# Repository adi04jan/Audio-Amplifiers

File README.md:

# Audio-Amplifiers
Audio Amplifier for creating a bass through low pass filter effect.

**IDE Used** : : [Autodesk Eagle](https://www.autodesk.com/products/eagle/overview)

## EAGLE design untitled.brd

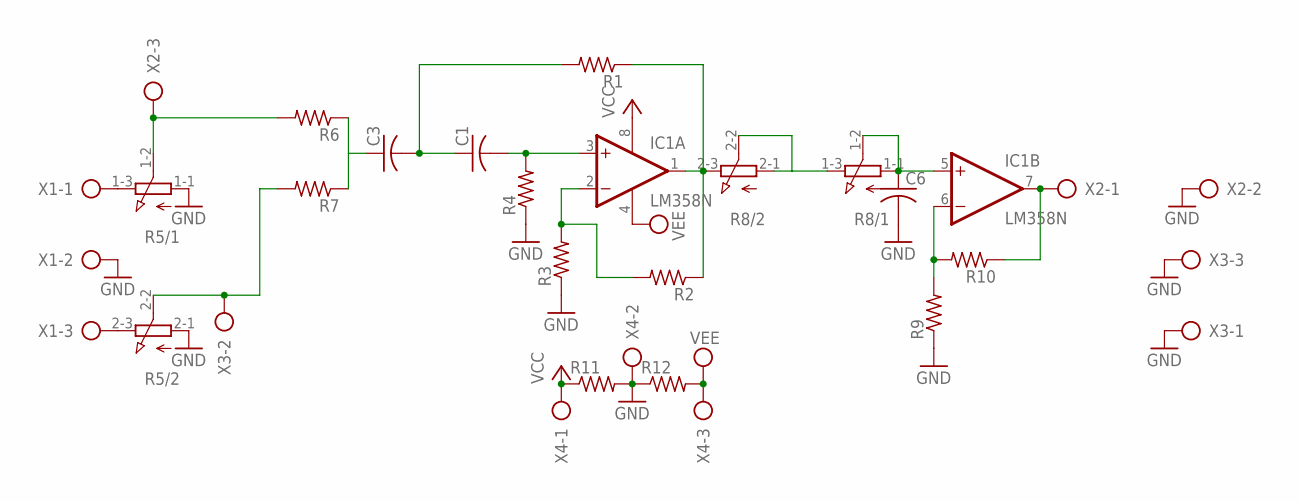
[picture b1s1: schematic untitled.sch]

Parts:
C1, C3, C6: C-US025-025X050; C025-025X050
IC1: LM358N; DIL08
R1, R2, R3, R4, R6, R7, R9, R10: FLIPFLOP-RES; 0805-THM
R5, R8: 3RP/1610G
R11, R12: R-US_0309/10; 0309/10
X1, X2, X3, X4: AK300/3

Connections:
GND: C6.2, R3.1, R4.1, R5.1-1 (A), R5.2-1 (A), R9.1, R11.2, R12.1, X1.2, X2.2, X3.1, X3.3, X4.2
unnamed: C1.2, IC1.3 (+IN), R4.2
unnamed: C1.1, C3.2, R1.2
unnamed: IC1.2 (-IN), R2.2, R3.2
unnamed: IC1.1 (OUT), R1.1, R2.1, R8.2-3 (E)
unnamed: R5.1-3 (E), X1.1
unnamed: R5.2-3 (E), X1.3
unnamed: C3.1, R6.1, R7.1
unnamed: R5.1-2 (S), R6.2, X2.3
unnamed: R5.2-2 (S), R7.2, X3.2
unnamed: C6.1, IC1.5 (+IN), R8.1-1 (A), R8.1-2 (S)
unnamed: R8.1-3 (E), R8.2-1 (A), R8.2-2 (S)
unnamed: IC1.6 (-IN), R9.2, R10.2
unnamed: IC1.7 (OUT), R10.1, X2.1
VCC: IC1.8 (V+), R11.1, X4.1
VEE: IC1.4 (V-), R12.2, X4.3

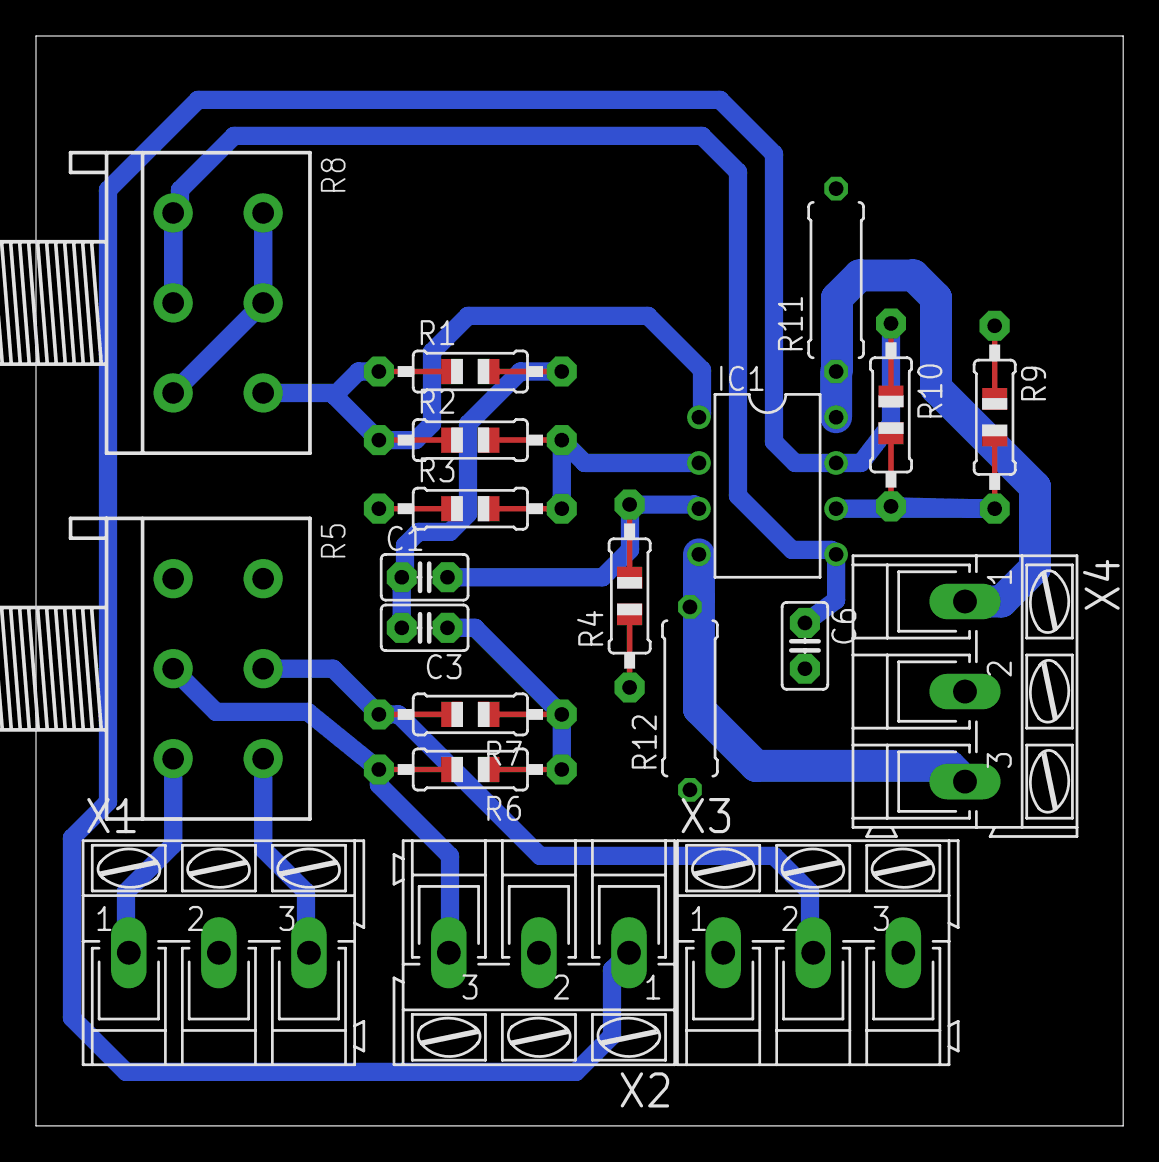
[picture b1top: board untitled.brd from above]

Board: 2 copper layers, 60.4 x 60.5 mm, 20 parts (0 on the bottom side), 16 nets.

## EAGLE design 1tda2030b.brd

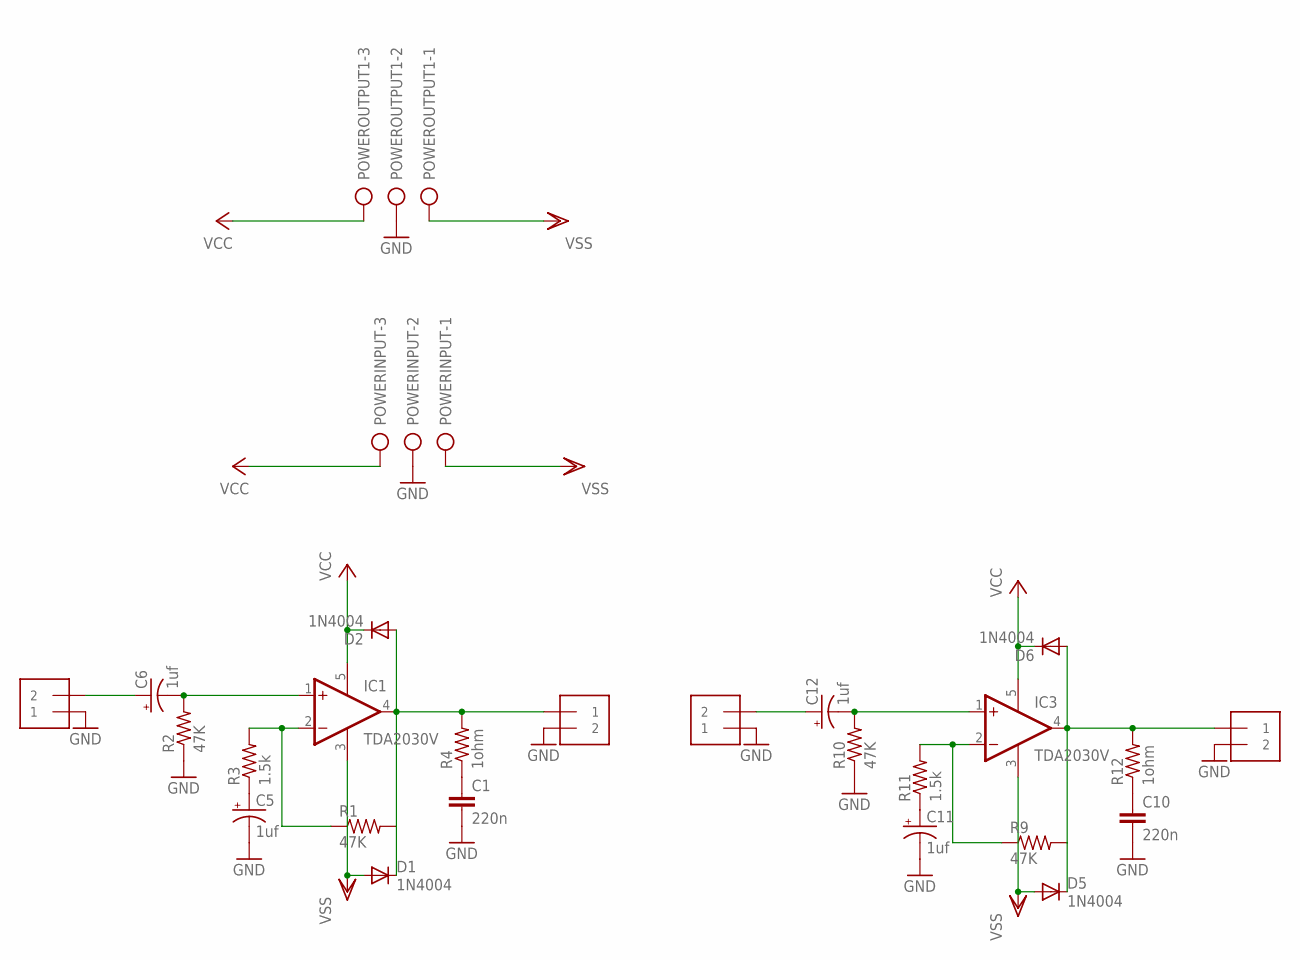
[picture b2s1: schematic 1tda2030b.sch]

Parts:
1STI/P, 1STO/P, 2NDI/P, 2NDO/P: 1X2-3.5MM
C1, C10: 220n; CAP-PTH-SMALL-KIT
C5, C6, C11, C12: 1uf; E5-8,5
D1, D2, D5, D6: 1N4004; DO41-10
IC1, IC3: TDA2030V; CB360
POWERINPUT: AK300/3
POWEROUTPUT1: AK300/3
R1, R2, R9, R10: 47K; 0805-THM
R3, R11: 1.5k; 0805-THM
R4, R12: 1ohm; 0805-THM

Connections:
GND: 1STI/P.1, 1STO/P.2, 2NDI/P.1, 2NDO/P.2, C1.2, C5.-, C10.2, C11.-, POWERINPUT.2, POWEROUTPUT1.2, R2.1, R10.1
unnamed: 1STO/P.1, D1.C, D2.A, IC1.4 (OUT), R1.2, R4.2
unnamed: C5.+, R3.1
unnamed: IC1.2 (-IN), R1.1, R3.2
unnamed: C1.1, R4.1
unnamed: 1STI/P.2, C6.+
unnamed: C6.-, IC1.1 (+IN), R2.2
unnamed: 2NDO/P.1, D5.C, D6.A, IC3.4 (OUT), R9.2, R12.2
unnamed: C11.+, R11.1
unnamed: IC3.2 (-IN), R9.1, R11.2
unnamed: C10.1, R12.1
unnamed: C12.-, IC3.1 (+IN), R10.2
unnamed: 2NDI/P.2, C12.+
VCC: D2.C, D6.C, IC1.5 (V+), IC3.5 (V+), POWERINPUT.3, POWEROUTPUT1.3
VSS: D1.A, D5.A, IC1.3 (GND), IC3.3 (GND), POWERINPUT.1, POWEROUTPUT1.1

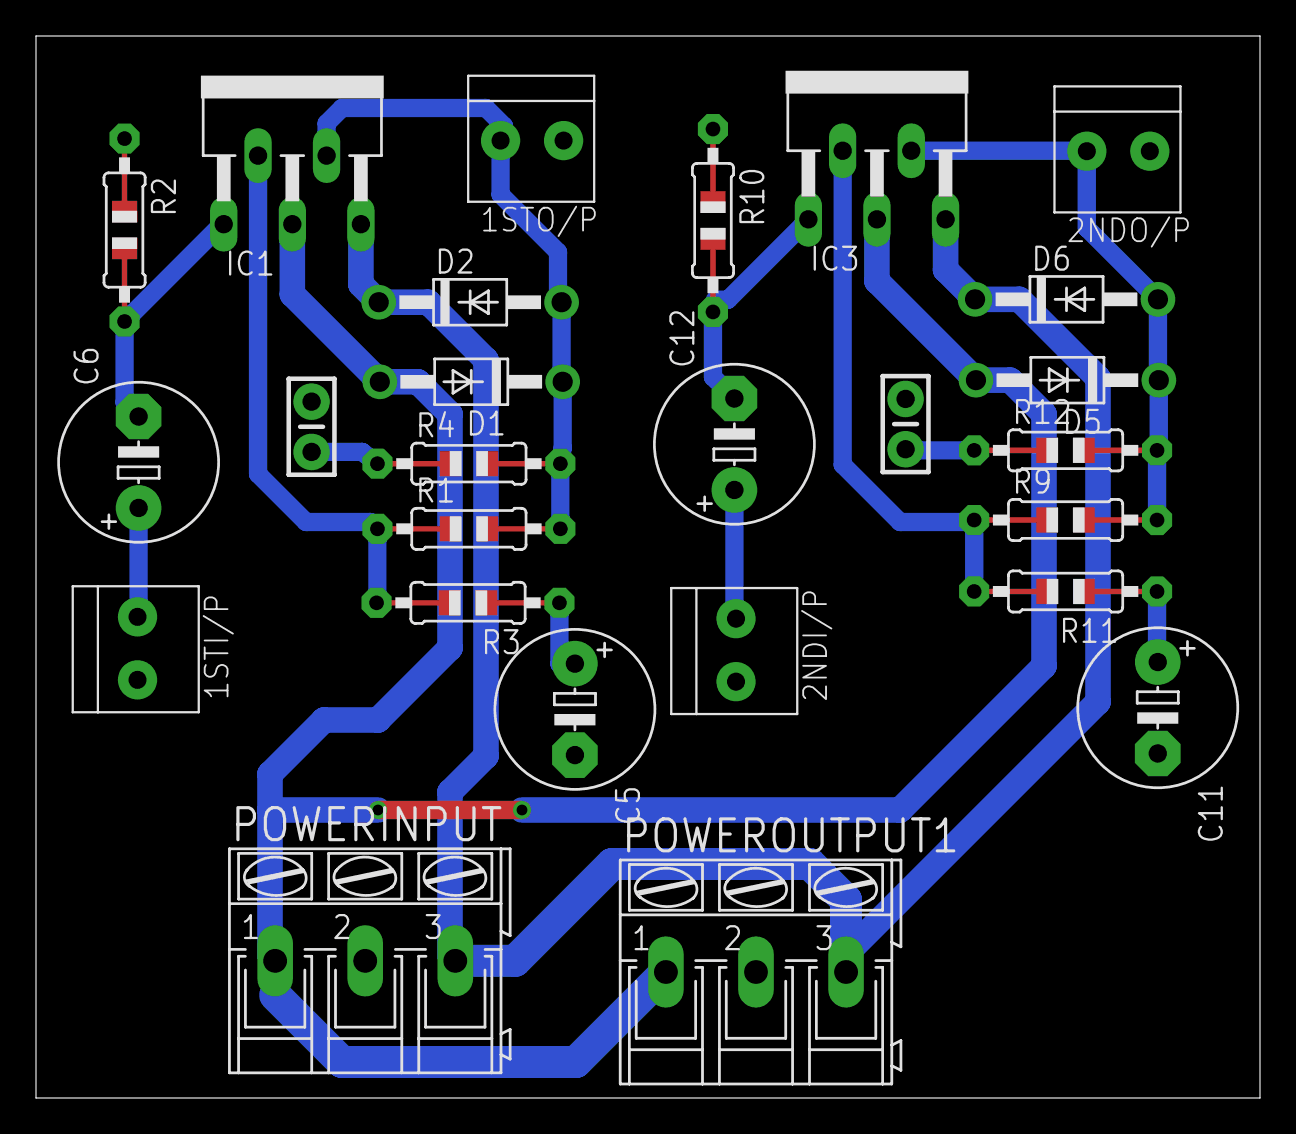
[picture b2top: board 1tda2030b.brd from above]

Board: 2 copper layers, 68.0 x 59.0 mm, 26 parts (0 on the bottom side), 15 nets.

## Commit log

2017-02-10 TDA 2030 Stereo Amplifier
    this circuit is based on Tda 2030 which is a monolithic class AB amplifier uses a bridge power source of 12v ,0v and -12v .
    In the above circuit pin 1 of power connector is negative voltage and pin 3 is positive voltage.
    above circuit give nearly 12w power rating great for audio purpose.
    dimensions:- 59cm X 69cm
    **HEATSINK IS NEEDED FOR PROPER USE**
2017-02-10 Low Pass Filter or Bass Filter
    This circuit allow to pass only low frequency.
    Circuit use lm358 at core and can be replaced by any other op-amp
    It can be used as a pre-amp for Power amplifier.
    input voltage = +-12v DC
    gain is adjustable
    2 knob for volume and setting cutoff frequency

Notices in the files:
parts and their libraries:
SparkFun-Capacitors: Licensing: Creative Commons ShareAlike 4.0 International - https://creativecommons.org/licenses/by-sa/4.0
